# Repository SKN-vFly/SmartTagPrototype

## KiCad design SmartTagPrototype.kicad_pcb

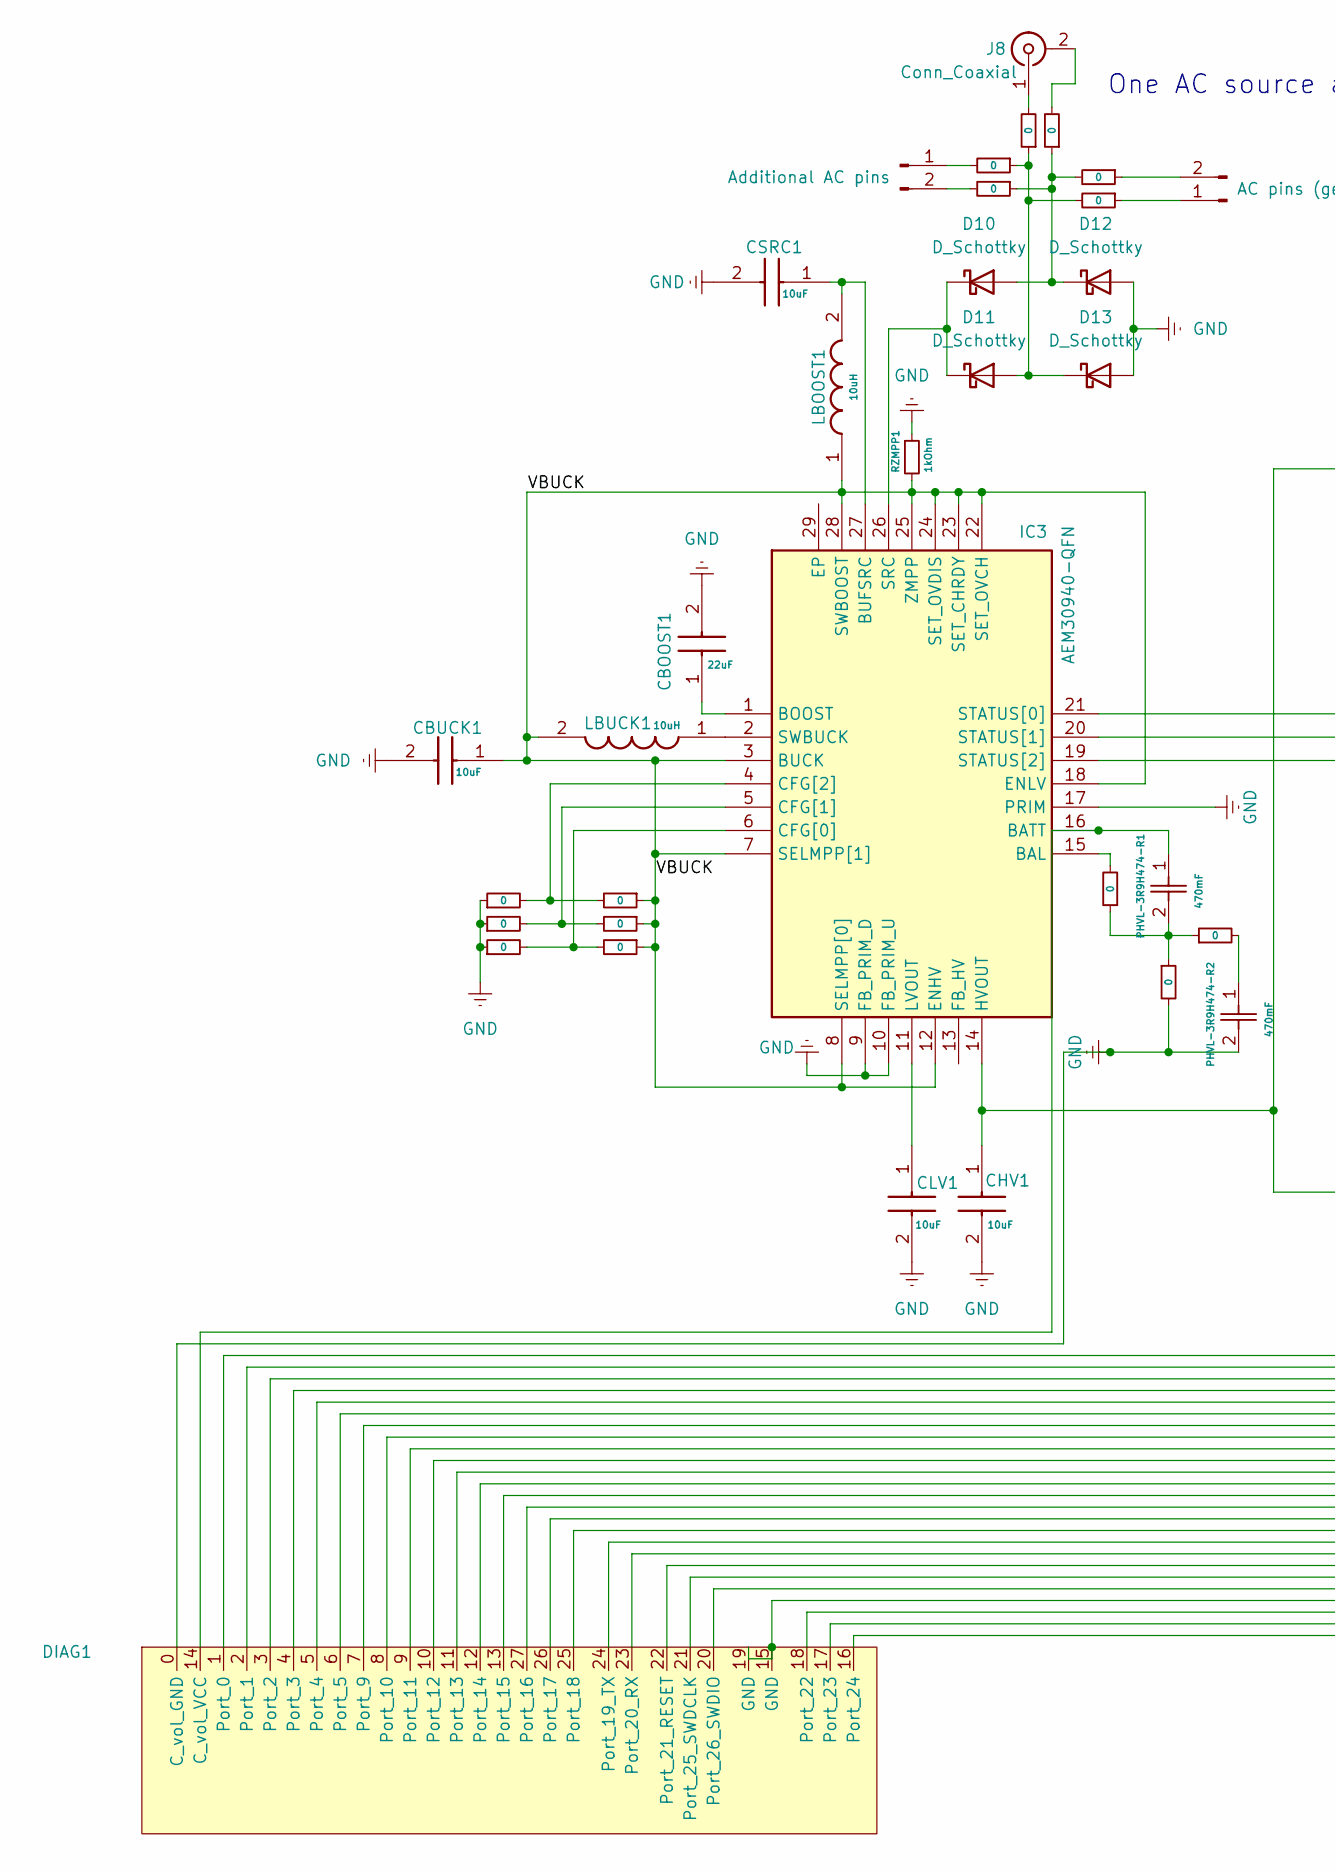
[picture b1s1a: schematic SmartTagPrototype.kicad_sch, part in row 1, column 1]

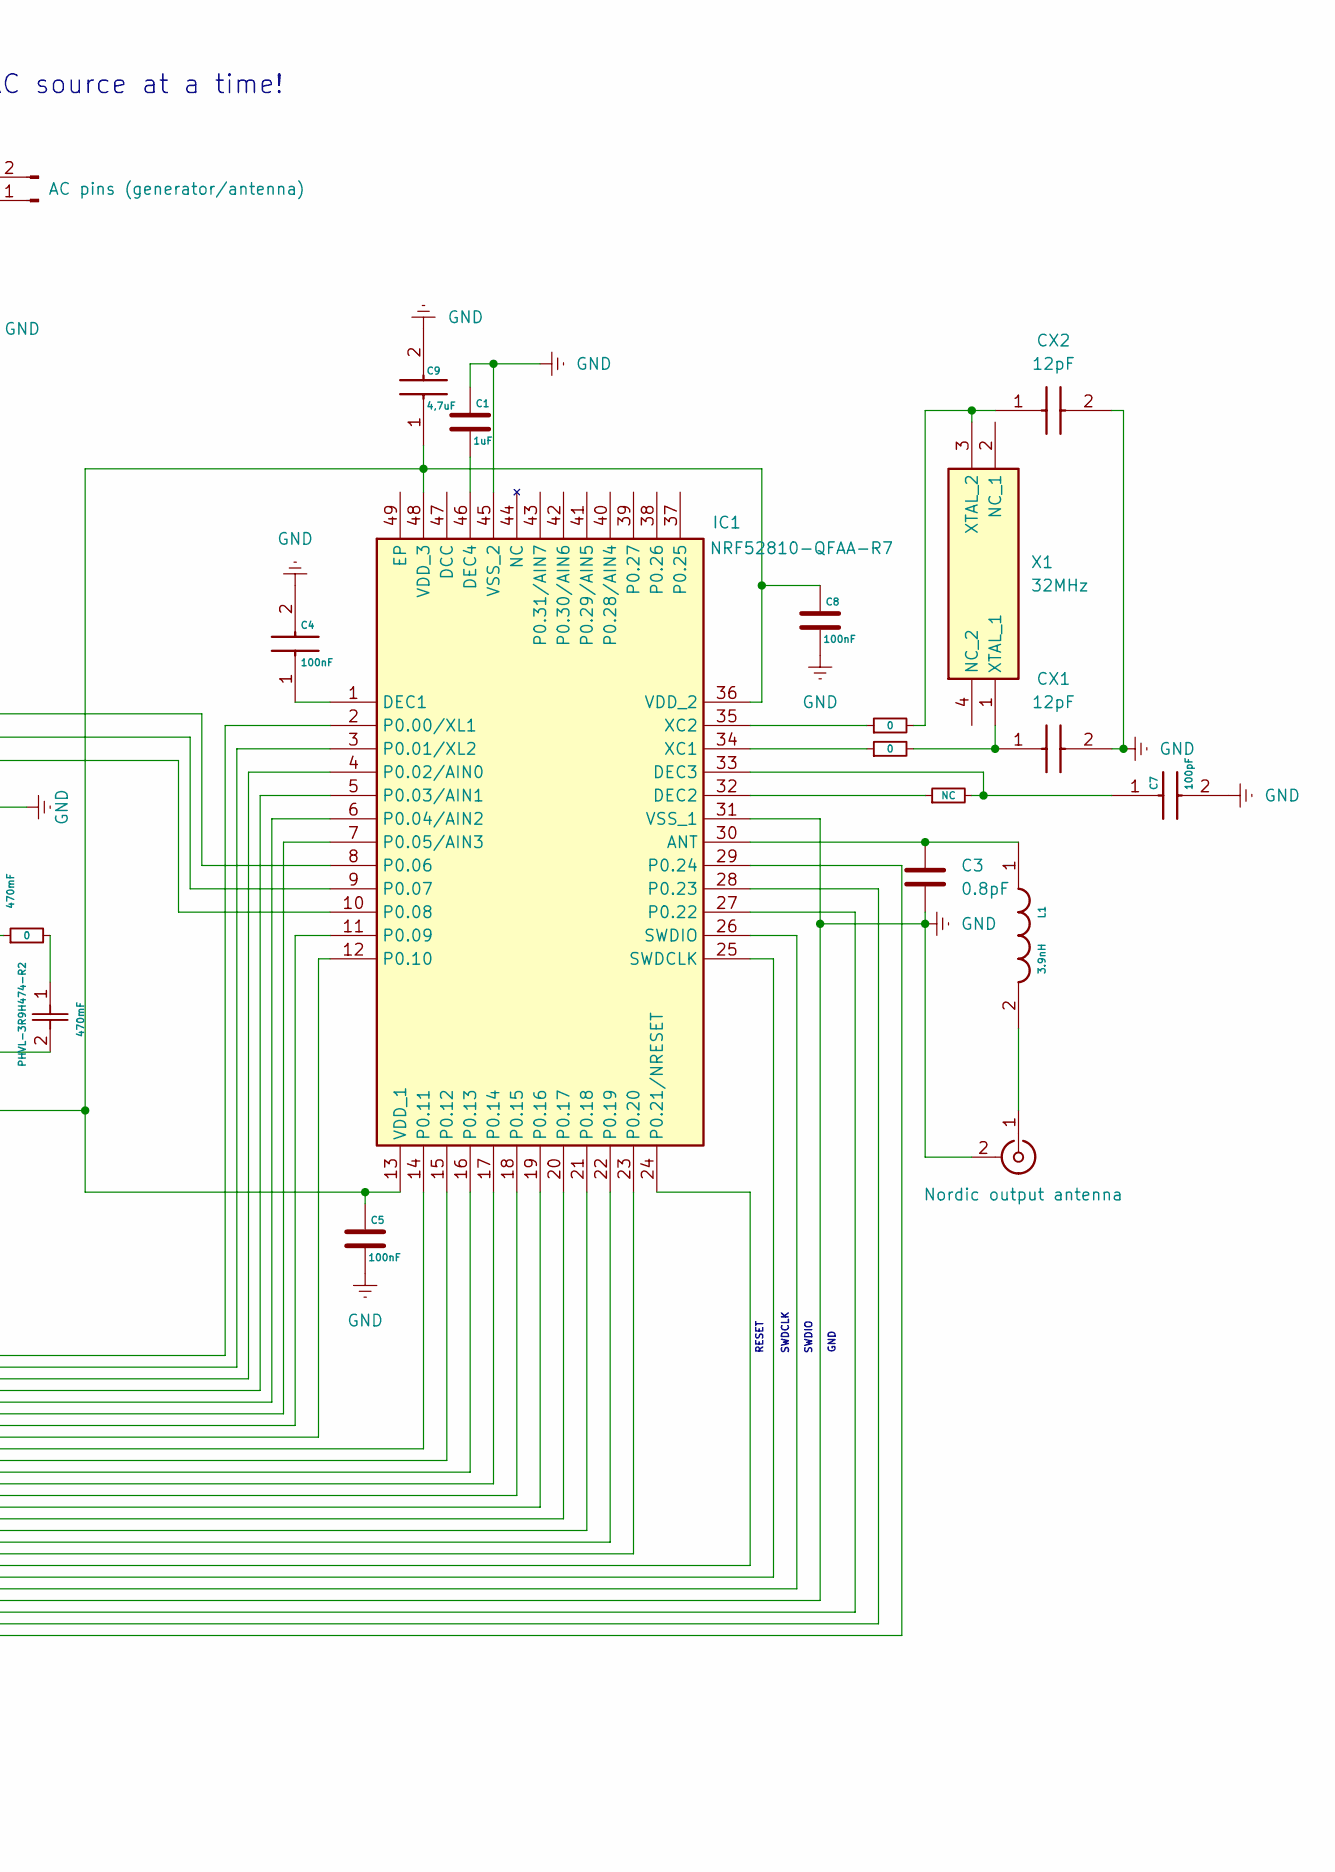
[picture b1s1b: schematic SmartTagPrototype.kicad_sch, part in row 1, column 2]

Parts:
C1: 1uF; CP_Radial_D5.0mm_P2.50mm
C3: 0.8pF; C_2.8x1
C4: 100nF; CP_Radial_D5.0mm_P2.50mm; Manufacturer_Part_Number 0402X7R104KT2AT; Mouser Part Number 581-0402X7R104KT2AT
C5, C8: 100nF; CP_Radial_D5.0mm_P2.50mm
C7: 100pF; CP_Radial_D5.0mm_P2.50mm; Manufacturer_Part_Number 0201ZA101JAT2A; Mouser Part Number 581-0201ZA101JAT2A
C9: 4,7uF; CP_Radial_D4.0mm_P2.00mm; Manufacturer_Part_Number LMK107BJ475KA-T; Mouser Part Number 963-LMK107BJ475KA-T
CBOOST1: 22uF; CP_Radial_D4.0mm_P2.00mm; Manufacturer_Part_Number GRM188C61C226ME01J; Mouser Part Number 81-GRM188C61C226ME1J
CBUCK1: 10uF; CP_Radial_D4.0mm_P2.00mm; Manufacturer_Part_Number KGM03DR50G106MH; Mouser Part Number 581-KGM03DR50G106MH
CHV1: 10uF; CP_Radial_D4.0mm_P2.00mm; Manufacturer_Part_Number KGM03DR50G106MH; Mouser Part Number 581-KGM03DR50G106MH
CLV1: 10uF; CP_Radial_D4.0mm_P2.00mm; Manufacturer_Part_Number KGM03DR50G106MH; Mouser Part Number 581-KGM03DR50G106MH
CSRC1: 10uF; CP_Radial_D4.0mm_P2.00mm; Manufacturer_Part_Number KGM03DR50G106MH; Mouser Part Number 581-KGM03DR50G106MH
CX1, CX2: 12pF; C_2.8x1; Manufacturer_Part_Number 06035U120GAT2A; Mouser Part Number 581-06035U120GAT2A
D10, D11, D12, D13: D_Schottky; D_SOD-323F
DIAG1: DIAG
IC1: NRF52810-QFAA-R7; QFN-48_EP_6x6_Pitch0.4mm; Manufacturer_Part_Number NRF52810-QFAA-R7; Mouser Part Number 949-NRF52810-QFAA-R7
IC3: AEM30940-QFN; QFN-28_EP_5.75x5.75_Pitch0.5mm; Manufacturer_Part_Number AEM30940-QFN; Mouser Part Number 120-AEM30940-QFN
J1: Nordic output antenna; U_FL
J7: Additional AC pins; PinHeader_1x02_P2.54mm_Vertical
J8: Conn_Coaxial; U_FL
J9: AC pins (generator/antenna); PinHeader_1x02_P2.54mm_Vertical
L1: 3.9nH; SMD_2.0x1.0; Manufacturer_Part_Number LQW18AS3N9J0ZD; Mouser Part Number 81-LQW18AS3N9J0ZD
LBOOST1: 10uH; SMD_1.6_1.5; Manufacturer_Part_Number LQM18DZ100M70L; Mouser Part Number 81-LQM18DZ100M70L
LBUCK1: 10uH; SMD_1.6_1.5; Manufacturer_Part_Number LQM18DZ100M70L; Mouser Part Number 81-LQM18DZ100M70L
PHVL-3R9H474-R1, PHVL-3R9H474-R2: 470mF; CP_Radial_D5.0mm_P2.50mm
R1, R2, R3, R4, R5, R6, R7, R8, R9, R10, R11, R12, R13, R15, R16, R17, R18: 0; SolderJumper-2_P1.3mm_Open_TrianglePad1.0x1.5mm
R14: NC; SolderJumper-2_P1.3mm_Open_TrianglePad1.0x1.5mm
RZMPP1: 1kOhm; R_0201_0603Metric
X1: 32MHz; Murata; Manufacturer_Part_Number XRCGB32M000F1S2AR0; Mouser Part Number 81-XRCGB32M000F1S2AR

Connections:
/VBUCK: CBUCK1.1, IC3.3 (BUCK), IC3.7 (SELMPP[1]), IC3.8 (SELMPP[0]), IC3.12 (ENHV), IC3.18 (ENLV), IC3.22 (SET_OVCH), IC3.23 (SET_CHRDY), IC3.24 (SET_OVDIS), IC3.25 (ZMPP), IC3.28 (SWBOOST), LBOOST1.1, LBUCK1.2, R15.1, R16.1, R17.1, RZMPP1.2
GND: C1.1, C3.2, C4.2, C5.2, C7.2, C8.2, C9.2, CBOOST1.2, CBUCK1.2, CHV1.2, CLV1.2, CSRC1.2, CX1.2, CX2.2, D12.2 (A), D13.2 (A), DIAG1.0 (C_vol_GND), DIAG1.15 (GND), DIAG1.19 (GND), IC1.31 (VSS_1), IC1.45 (VSS_2), IC3.9 (FB_PRIM_D), IC3.10 (FB_PRIM_U), IC3.17 (PRIM), J1.2 (Ext), PHVL-3R9H474-R2.2, R4.1, R5.1, R6.1, R9.2, RZMPP1.1; also elsewhere on the board
unnamed: D10.2 (A), D12.1 (K), R2.1, R3.2, R13.1
unnamed: D10.1 (K), D11.1 (K), IC3.26 (SRC)
unnamed: D11.2 (A), D13.1 (K), R1.1, R12.1, R18.2
unnamed 5: DIAG1.14 (C_vol_VCC), IC3.16 (BATT), PHVL-3R9H474-R1.1; also elsewhere on the board
unnamed: DIAG1.1 (Port_0), IC1.2 (P0.00/XL1)
unnamed: DIAG1.2 (Port_1), IC1.3 (P0.01/XL2)
unnamed: DIAG1.3 (Port_2), IC1.4 (P0.02/AIN0)
unnamed: DIAG1.4 (Port_3), IC1.5 (P0.03/AIN1)
unnamed: DIAG1.5 (Port_4), IC1.6 (P0.04/AIN2)
unnamed: DIAG1.6 (Port_5), IC1.7 (P0.05/AIN3)
unnamed: DIAG1.7 (Port_9), IC1.11 (P0.09)
unnamed: DIAG1.8 (Port_10), IC1.12 (P0.10)
unnamed: DIAG1.9 (Port_11), IC1.14 (P0.11)
unnamed: DIAG1.10 (Port_12), IC1.15 (P0.12)
unnamed: DIAG1.11 (Port_13), IC1.16 (P0.13)
unnamed: DIAG1.12 (Port_14), IC1.17 (P0.14)
unnamed: DIAG1.13 (Port_15), IC1.18 (P0.15)
unnamed: DIAG1.27 (Port_16), IC1.19 (P0.16)
unnamed: DIAG1.26 (Port_17), IC1.20 (P0.17)
unnamed: DIAG1.25 (Port_18), IC1.21 (P0.18)
unnamed: DIAG1.24 (Port_19_TX), IC1.22 (P0.19)
unnamed: DIAG1.23 (Port_20_RX), IC1.23 (P0.20)
unnamed: DIAG1.22 (Port_21_RESET), IC1.24 (P0.21/NRESET)
unnamed: DIAG1.18 (Port_22), IC1.27 (P0.22)
unnamed: DIAG1.17 (Port_23), IC1.28 (P0.23)
unnamed: DIAG1.16 (Port_24), IC1.29 (P0.24)
unnamed: DIAG1.21 (Port_25_SWDCLK), IC1.25 (SWDCLK)
unnamed: DIAG1.20 (Port_26_SWDIO), IC1.26 (SWDIO)
unnamed: C3.1, IC1.30 (ANT), L1.1
unnamed: C4.1, IC1.1 (DEC1)
unnamed: IC1.32 (DEC2), R14.1
unnamed: C7.1, IC1.33 (DEC3), R14.2
unnamed: C1.2, IC1.46 (DEC4)
unnamed: IC1.8 (P0.06), IC3.21 (STATUS[0])
unnamed: IC1.9 (P0.07), IC3.20 (STATUS[1])
unnamed: IC1.10 (P0.08), IC3.19 (STATUS[2])
unnamed: C5.1, C8.1, C9.1, CHV1.1, IC1.13 (VDD_1), IC1.36 (VDD_2), IC1.48 (VDD_3), IC3.14 (HVOUT)
unnamed: IC1.34 (XC1), R10.1
unnamed: IC1.35 (XC2), R11.1
unnamed: IC3.15 (BAL), R7.2
unnamed: CBOOST1.1, IC3.1 (BOOST)
unnamed: CSRC1.1, IC3.27 (BUFSRC), LBOOST1.2
unnamed: IC3.6 (CFG[0]), R6.2, R17.2
unnamed: IC3.5 (CFG[1]), R5.2, R16.2
unnamed: IC3.4 (CFG[2]), R4.2, R15.2
unnamed: CLV1.1, IC3.11 (LVOUT)
unnamed: IC3.2 (SWBUCK), LBUCK1.1
unnamed: J1.1 (In), L1.2
unnamed: J7.1, R1.2
unnamed: J7.2, R2.2
unnamed: J8.2 (Ext), R13.2
unnamed: J8.1 (In), R12.2
unnamed: J9.1, R18.1
unnamed: J9.2, R3.1
unnamed 56: PHVL-3R9H474-R1.2, R7.1, R8.1, R9.1; also elsewhere on the board
unnamed 57: PHVL-3R9H474-R2.1, R8.2; also elsewhere on the board
unnamed: CX1.1, R10.2, X1.1 (XTAL_1)
unnamed: CX2.1, R11.2, X1.3 (XTAL_2)

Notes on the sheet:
One AC source at a time!
SWDCLK
GND
SWDIO
RESET

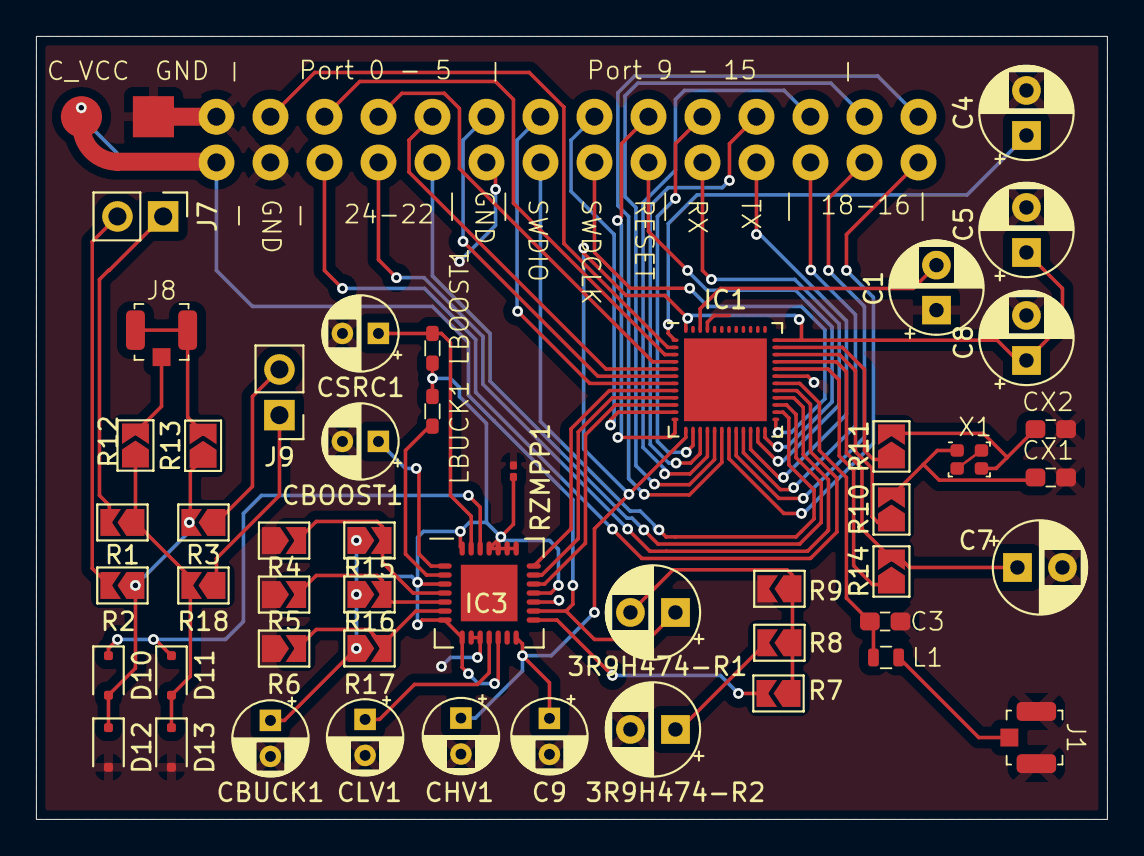
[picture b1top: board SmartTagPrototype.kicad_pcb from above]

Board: 2 copper layers, 59.5 x 43.5 mm, 50 parts (0 on the bottom side), 60 nets.

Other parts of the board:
3R9H474-R1, 3R9H474-R2: 470mF; CP_Radial_D5.0mm_P2.50mm

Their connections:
GND: 3R9H474-R2.2; also elsewhere on the board
unnamed 5: 3R9H474-R1.1; also elsewhere on the board
unnamed 56: 3R9H474-R1.2; also elsewhere on the board
unnamed 57: 3R9H474-R2.1; also elsewhere on the board

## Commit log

2025-02-03 dodanie footprintow do kondensatorow
2025-02-03 Updated sch
2025-02-03 Updated schema
2025-02-03 U_FL footprint
2025-02-03 dodane gniazda i rezystory, cewki ciagle do zrobienia
2025-02-03 dobra, dodalem cewki. Ide spac
2025-02-03 jeszcze kondensator zgubilem, teraz jest WSZYSTKO (punkty testowe kiedy indziej sie zrobi)
2025-02-04 wstępnie poukładane pcb
2025-02-04 sciezki przy aemie / PCB
2025-02-04 przed wylaniem masy / PCB
2025-02-04 ala gotowe PCB, wylane masy
2025-02-04 push abominacji czytaj dodany footprint i symbol zlacza testowego (niech Bog ma mnie w opiece)
2025-02-14 diag dodany, finish /PCB
2025-05-12 code BLE
2025-05-12 clean
